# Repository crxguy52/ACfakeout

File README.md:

For faking out AC pressure sensor

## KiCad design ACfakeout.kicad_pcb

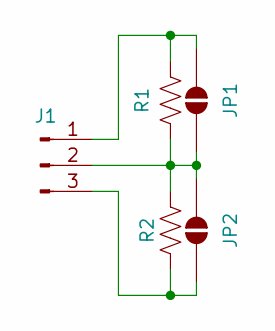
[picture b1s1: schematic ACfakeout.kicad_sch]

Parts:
J1: Conn_01x03_Pin; PinHeader_1x03_P2.54mm_Vertical
JP1, JP2: SolderJumper_2_Open; SolderJumper-2_P1.3mm_Open_Pad1.0x1.5mm
R1, R2: R_US; R_1206_3216Metric_Pad1.30x1.75mm_HandSolder

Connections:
unnamed: J1.1, JP1.2 (B), R1.2
unnamed: J1.2, JP1.1 (A), JP2.2 (B), R1.1, R2.2
unnamed: J1.3, JP2.1 (A), R2.1

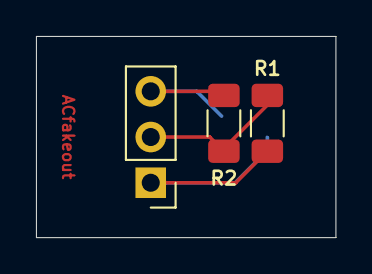
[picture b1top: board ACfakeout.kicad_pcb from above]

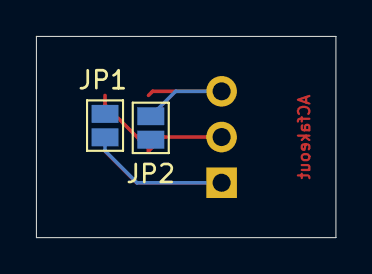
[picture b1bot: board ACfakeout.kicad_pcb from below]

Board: 2 copper layers, 16.6 x 11.2 mm, 5 parts (2 on the bottom side), 3 nets.
